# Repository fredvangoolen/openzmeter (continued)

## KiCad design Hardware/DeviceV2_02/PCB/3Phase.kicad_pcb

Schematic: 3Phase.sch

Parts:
BT1: JST 2mm-2P; JST_PH_B2B-PH-K_1x02_P2.00mm_Vertical
BZ1: QMB-09B-05; Buzzer_9x5.5RM4
C1, C2, C3, C4, C5, C6, C7, C10, C13, C14, C16, C17, C19, C20, C21, C22, C23, C24, C25, C26, C27, C28, C29, C30, C33, C34, C35, C36, C37: 100nF 25v; R_0603_1608Metric
C8, C9: 4.7uF 450v (10x12mm); CP_Radial_D10.0mm_P5.00mm
C11: 4.7uF 25v; C_0805_2012Metric
C12: 47uF 35v; CP_Radial_D5.0mm_P2.50mm
C15, C18, C31, C32: 100uF 16v; CP_Radial_D5.0mm_P2.50mm
D1, D3: ES1J; D_SMA
D2: BZT52C15S; D_SOD-323
D4, D5, D6: 1N4007G; D_SMA
D8: SS14; D_SMA
D9, D10, D12: 3mm bicolor LED; LED_D3.0mm
D11: 3mm blue LED; LED_D3.0mm
D13, D14: 1N5819WS; D_SOD-323
J1, J2, J3, J4: 95001-6P6C; KF2EDGR_2.54x4
J5: 2.54x3 pin header; PinHeader_1x03_P2.54mm_Vertical
J6: JST 2mm-2P; JST_PH_B2B-PH-K_1x02_P2.00mm_Vertical
JP1: 2.54x3 pin header; PinHeader_1x03_P2.54mm_Vertical
L1: 470uH 350mA; L_Axial_L12.0mm_D5.0mm_P5.08mm_Vertical_Fastron_MISC
L2: 1mH 300mA; CD75_7.8x7.0
L3: 10uH; CD43_4.5x4.0
L4: 2.2uH; CD32_3.5x3.0
P1: 3.81x4 terminal block; PhoenixContact_MC_1,5_4-G-3.81_1x04_P3.81mm_Horizontal
P2: 2 x 2.54x2 pin header; NanoPI Air
Q1: AP2301; SOT-23
Q2, Q3: 2N7002; SOT-23
R1, R2, R6, R9, R11, R13, R19, R20: 1k02; R_0603_1608Metric
R3, R7, R8, R14, R62, R63, R64: 100h; R_0603_1608Metric
R4, R5, R10, R12, R15, R16, R17, R22: 1k69; R_0603_1608Metric
R18, R21, R24, R25, R26, R27, R28, R29, R30: 200k; R_1206_3216Metric
R23, R35, R39, R40, R51, R52: 4k7; R_0603_1608Metric
R31, R32, R34: 2.2k; R_0603_1608Metric
R33: 36k5; R_0603_1608Metric
R36, R41, R42, R45, R46, R47, R48, R49, R57, R65, R66: 270k; R_0603_1608Metric
R37, R44, R56: 100k; R_0603_1608Metric
R38: 39h; R_0603_1608Metric
R43, R53, R54, R58: 1k43; R_0603_1608Metric
R50: 51k; R_0603_1608Metric
R55: 220h; R_0603_1608Metric
RV1: 05D391K; RV_Disc_D7mm_W3.4mm_P5mm
SW2: SW_Push; SW_Tactile_SKHH_Angled
TH1: NTC 10D5; RV_Disc_D7mm_W3.4mm_P5mm
U1, U3, U11: MCP6004; SOIC-14_3.9x8.7mm_P1.27mm
U2, U4, U5: ME6216A33M3G; SOT-23
U6: VIPER22ADIP-E; DIP-8_W7.62mm
U7: FP6715; TSOT-23-6
U8: SRV05-4; SOT-23-6
U9: 74HC4066; TSSOP-14_4.4x5mm_P0.65mm
U10: SY8201ABC; TSOT-23-6
U12: TP4054ST25P; SOT-23-5
U13: STM32F042; LQFP-32_7x7mm_Pitch0.8mm

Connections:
20v: C12.1, C17.1, D3.2 (A), L2.2, R40.1, U10.4 (EN), U10.5 (IN)
+1V65: C27.1, C33.1, C34.1, R5.2, R16.2, R17.2, R22.2, R31.2, R32.2, R34.2, R41.1, R42.1, R45.2, R46.2, R47.2, R48.2, R65.1, R66.1, U11.13 (-), U11.14, U13.7 (PA1)
+3.3VA: C1.1, C22.1, C32.1, R51.2, U2.2 (VO), U13.5 (VDDA)
+3V3: C23.1, C24.1, C31.1, R35.2, SW2.1, U4.2 (VO), U8.5, U13.1 (VDD), U13.17 (VDDIO2)
+5V: BZ1.1 (-), C14.1, C15.1, C25.2, C26.2, C30.2, C35.1, D13.2 (A), J6.1, JP1.3, P2.Vcc, R49.2, U1.4 (V+), U3.4 (V+), U5.3 (VI), U7.5 (OUT), U9.14 (V+), U11.4 (V+)
BAT_ADC: C37.1, R56.1, R57.1, U13.15 (ADC9)
CHRG: U12.1 (~CHRG), U13.18 (PA8)
GAIN_SW: U9.5 (ON), U9.6 (ON), U9.12 (ON), U9.13 (ON), U13.3 (PF1)
GND: BT1.2 (-), C1.2, C2.2, C3.2, C4.2, C6.2, C7.2, C8.2, C9.2, C12.2, C13.2, C14.2, C15.2, C16.2, C17.2, C18.2, C19.2, C20.2, C21.2, C22.2, C23.2, C24.2, C25.1, C26.1, C27.2, C28.1, C29.2, C30.1, C31.2, C32.2, C33.2, C34.2, C35.2, C36.2, C37.2, D1.2 (A), D11.1 (K), J1.1, J2.1, J3.1, J4.1, J5.3, P1.4, P2.GND, Q2.2 (S), Q3.2 (S), R23.2, R33.1, R37.1, R40.2, R44.1, R50.2, R52.2, R57.2, RV1.1, U1.11 (V-), U2.1 (GND), U3.11 (V-), U4.1 (GND), U5.1 (GND), U7.2 (GND), U8.2, U9.7 (V-), U10.2 (GND), U11.11 (V-), U12.2 (GND), U13.16 (GND), U13.32 (GND)
IN_L1: D6.2 (A), P1.3, R24.2
IN_L2: D5.2 (A), P1.2, R18.2
IN_L3: D4.2 (A), P1.1, R21.2
L1I_ADC: C6.1, R8.1, U8.1, U13.11 (ADC5)
L1V_ADC: C19.1, R62.1, U13.8 (ADC2)
L2I_ADC: C4.1, R3.1, U8.3, U13.12 (ADC6)
L2V_ADC: C20.1, R63.1, U13.9 (ADC3)
L3I_ADC: C2.1, R7.2, U8.6, U13.13 (ADC7)
L3V_ADC: C21.1, R64.1, U13.10 (ADC4)
NI_ADC: C7.1, R14.1, U8.4, U13.14 (ADC8)
unnamed: BT1.1 (+), Q1.3 (D), R56.2, U12.3 (OUT)
unnamed: BZ1.2 (+), Q2.3 (D)
unnamed: C5.1, L4.1, U10.6 (LX)
unnamed: C5.2, U10.1 (BST)
unnamed: C8.1, L1.1, RV1.2, TH1.1
unnamed: C9.1, L1.2, U6.5 (D1), U6.6 (D2), U6.7 (D3), U6.8 (D4)
unnamed: C10.1, D2.2 (A), U6.3 (FB)
unnamed: C10.2, C11.2, D1.1 (K), L2.1, U6.1 (S1), U6.2 (S2)
unnamed: C11.1, D2.1 (K), D3.1 (K), U6.4 (VDD)
unnamed: C16.1, R51.1, R52.1, U11.12 (+)
unnamed: C28.2, R39.2, U13.6 (WKUP1)
unnamed: C29.1, D13.1 (K), D14.1 (K), U2.3 (VI), U4.3 (VI)
unnamed: C36.1, JP1.1, U5.2 (VO)
unnamed: D4.1 (K), D5.1 (K), D6.1 (K), TH1.2
unnamed: D9.1 (A1), U13.28 (PB5)
unnamed: D10.1 (A1), U13.27 (PB4)
unnamed: D9.2 (K), D10.2 (K), D12.2 (K), R38.2
unnamed: D11.2 (A), R55.2
unnamed: D12.1 (A1), U13.25 (PA15)
unnamed: J1.2, R65.2, U1.5 (+)
unnamed: J1.3, R66.2, U1.10 (+)
unnamed: J1.4, J2.4, J3.4, J4.4, JP1.2
unnamed: J2.2, R42.2, U1.3 (+)
unnamed: J2.3, R41.2, U1.12 (+)
unnamed: J3.2, R45.1, U3.5 (+)
unnamed: J3.3, R46.1, U3.10 (+)
unnamed: J4.2, R47.1, U3.3 (+)
unnamed: J4.3, R48.1, U3.12 (+)
unnamed: J5.1, U13.24 (SWDCK)
unnamed: J5.2, U13.23 (SWDIO)
unnamed: J6.2, Q3.3 (D)
unnamed: L3.2, U7.1 (LX)
unnamed: P2.DM, U13.21 (USB-)
unnamed: P2.DP, U13.22 (USB+)
unnamed: Q2.1 (G), U13.26 (PB3)
unnamed: Q3.1 (G), R44.2, U13.31 (PB8/BOOT0)
unnamed: R1.1, R2.1, U1.8
unnamed: R1.2, R4.2, U1.6 (-), U9.8
unnamed: R2.2, R5.1, R43.2, U1.9 (-)
unnamed: R4.1, R8.2, U1.7
unnamed: R6.1, R9.1, U1.14
unnamed: R10.1, R13.2, U3.6 (-), U9.2
unnamed: R7.1, R10.2, U3.7
unnamed: R11.1, R13.1, U3.8
unnamed: R11.2, R17.1, R54.2, U3.9 (-)
unnamed: R3.2, R12.1, U1.1
unnamed: R9.2, R12.2, U1.2 (-), U9.10
unnamed: R14.2, R15.1, U3.1
unnamed: R15.2, R20.2, U3.2 (-), U9.4
unnamed: R6.2, R16.1, R53.2, U1.13 (-)
unnamed: R18.1, R27.2
unnamed: R19.1, R20.1, U3.14
unnamed: R19.2, R22.1, R58.2, U3.13 (-)
unnamed: R21.1, R28.2
unnamed: R23.1, U12.5 (PROG)
unnamed: R24.1, R25.1
unnamed: R25.2, R29.2
unnamed: R26.1, R34.1, U11.10 (+)
unnamed: R26.2, R28.1
unnamed: R27.1, R30.2
unnamed: R29.1, R31.1, U11.3 (+)
unnamed: R30.1, R32.1, U11.5 (+)
unnamed: R35.1, U13.4 (~RST)
unnamed: R38.1, U13.20 (PA10)
unnamed: R39.1, SW2.2
unnamed: R43.1, U9.9
unnamed: R49.1, R50.1, U7.3 (FB)
unnamed: R53.1, U9.11
unnamed: R54.1, U9.1
unnamed: R55.1, U13.19 (PA9)
unnamed: R58.1, U9.3
unnamed: R62.2, U11.1, U11.2 (-)
unnamed: R63.2, U11.6 (-), U11.7
unnamed: R64.2, U11.8, U11.9 (-)
POWER: C13.1, D8.1 (K), D14.2 (A), L3.1, Q1.2 (S), U7.6 (VIN)
POWER_EN: R37.2, U7.4 (EN), U13.29 (PB6)

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
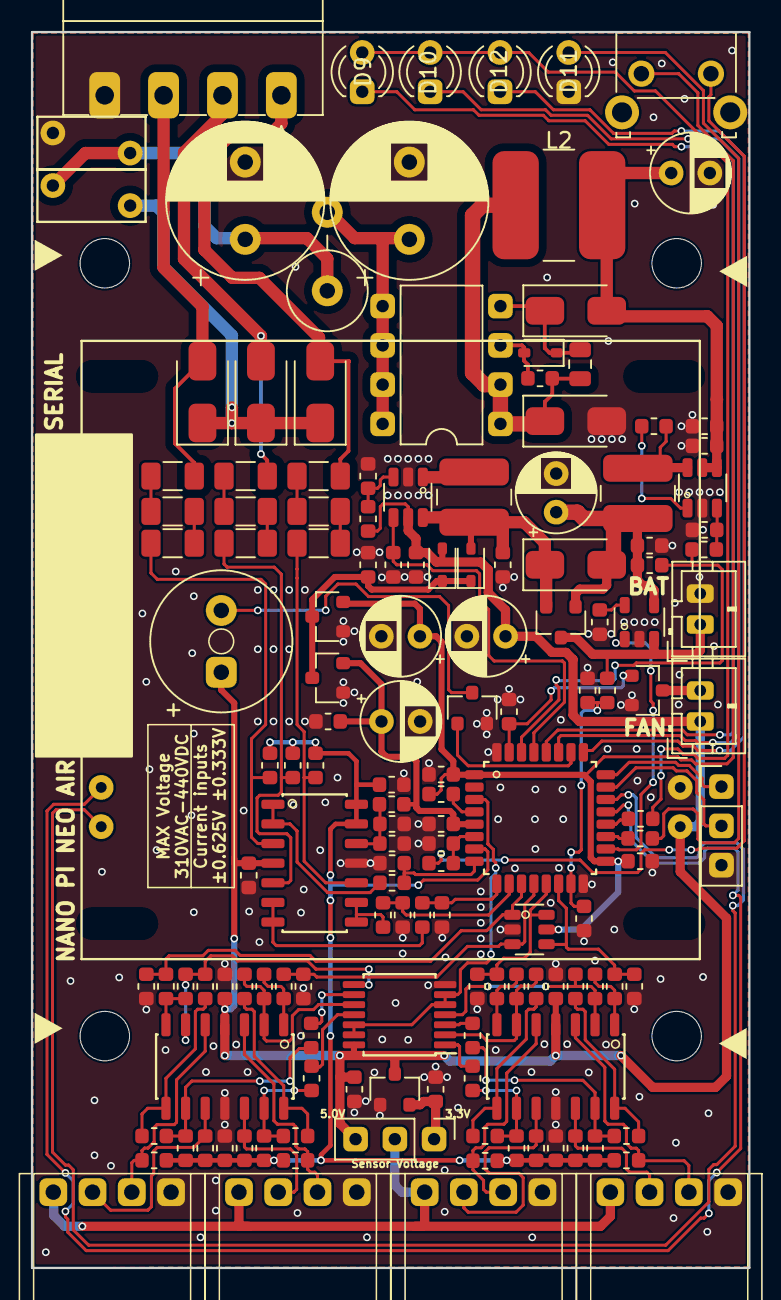
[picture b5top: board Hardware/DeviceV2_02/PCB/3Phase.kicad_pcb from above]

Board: 2 copper layers, 46.4 x 80.0 mm, 152 parts (0 on the bottom side), 98 nets.

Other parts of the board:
R59: 150k; R_0603_1608Metric
‣: MountingHole_3.2mm_M3
‣#2, ‣#3, ‣#4: MountingHole_3.2mm_M3

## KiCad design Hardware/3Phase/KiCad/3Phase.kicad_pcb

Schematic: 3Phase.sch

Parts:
BT1: Battery_Cell; JST_PH_B2B-PH-K_1x02_P2.00mm_Vertical
BZ1: Buzzer; Buzzer_12x9.5RM7.6
C1, C2, C4, C6, C7, C13, C14, C19, C20, C21, C22, C23, C25, C26, C27, C28, C29: 100nF; C_0603_1608Metric
C3, C17: 100nF 50v; C_0603_1608Metric
C5, C16, C24: C_Small; C_0603_1608Metric
C8, C9: 3.3uF 450v; CP_Radial_D10.0mm_P5.00mm
C10: 47nF 50v; C_0603_1608Metric
C11: 2.2uF 25v; C_0805_2012Metric
C12: 47uF 25v; CP_Radial_D5.0mm_P2.50mm
C15: 100uF 10v; CP_Radial_D4.0mm_P2.00mm
C18: 100uF 16v; CP_Radial_D5.0mm_P2.50mm
D1: ES1J; D_SMA
D2: BZT52C15S; D_SOD-323
D3: SF18; D_SMA
D4, D5, D6: 1N4007; D_SMA
D7: 1N4148; D_SOD-323
D8: SS14; D_SMA
D9, D10, D12: 3mm bicolor LED; LED_D3.0mm
D11: 3mm blue LED; LED_D3.0mm
D13, D14: 1N5819WS; D_SOD-323
J1, J2, J3, J4: 95001-6P6C; RJ11_4P4C
J5: Conn_01x03; PinHeader_1x03_P2.54mm_Vertical
L1: 470uH 350mA; L_Axial_L12.0mm_D5.0mm_P5.08mm_Vertical_Fastron_MISC
L2: 1mH 300mA; L_Radial_D10.5mm_P5.00mm_Abacron_AISR-01
L3: 10uH; CD43_4.5x4.0
L4: 2.2uH; CD32_3.5x3.0
L5: 10uH; L_0603_1608Metric
P1: CONN_01X04; PhoenixContact_MC_1,5_4-G-3.81_1x04_P3.81mm_Horizontal
P2: NanoPI AIR; NanoPI Air
Q1: Si2301DS; SOT-23
Q2: 2N7002; SOT-23
R1, R9, R33: 33k; R_0603_1608Metric
R2, R4, R5, R6, R11, R12, R16, R17, R23, R35, R39, R51, R52: 10k; R_0603_1608Metric
R3, R7, R8, R14, R62, R63, R64: 100h; R_0603_1608Metric
R10, R15, R19, R22: 10K; R_0603_1608Metric
R13, R20: 33K; R_0603_1608Metric
R18, R21, R24, R25, R26, R27, R28, R29, R30: 200k; R_1206_3216Metric
R31, R32, R34: 2.2k; R_0603_1608Metric
R36: 240k; R_0603_1608Metric
R37, R43, R44, R56: 100k; R_0603_1608Metric
R38: 180h; R_0603_1608Metric
R41, R42, R45, R46, R47, R48, R65, R66: 1M; R_0603_1608Metric
R49: 300k; R_0603_1608Metric
R50: 56k; R_0603_1608Metric
R55: 39h; R_0603_1608Metric
R57: 270k; R_0603_1608Metric
R58, R59, R60, R61: 1k5; R_0603_1608Metric
RV1: 07D431K; RV_Disc_D7mm_W3.6mm_P5mm
SW1: SW_Push; SW_SPST_FSMSM
SW2: SW_Push; SW_Tactile_SKHH_Angled
TH1: NTC 10D5; RV_Disc_D7mm_W3.6mm_P5mm
U1, U11: MCP6004; SOIC-14_3.9x8.7mm_P1.27mm
U2: 4066; SOIC-14_3.9x8.7mm_P1.27mm
U3: MCP6004; SOIC-14_3.9x8.7mm_Pitch1.27mm
U4: XC6206; SOT-23
U6: VIPer22; DIP-8_W7.62mm
U7: PS7516; TSOT-23-6
U10: SY8113; TSOT-23-6
U12: LTC4054; SOT-23-5
U13: STM32F042; LQFP-32_7x7mm_Pitch0.8mm

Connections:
15v: C12.1, C17.1, D3.2, L2.2, U10.4, U10.5
+1V65: R5.2, R16.2, R17.2, R22.2, R31.2, R32.2, R34.2, R41.1, R42.1, R45.2, R46.2, R47.2, R48.2, R65.1, R66.1, U11.1, U11.2 (-)
+3.3VA: C1.1, C22.1, C25.2, C26.2, C27.1, L5.2, R51.2, U1.4 (V+), U2.14 (V+), U3.4 (V+), U11.4 (V+), U13.5 (VDDA)
+3V3: C23.1, C24.1, L5.1, R35.2, R43.1, U4.2, U13.1 (VDD), U13.17 (VDDIO2)
+5V: BZ1.1, C14.1, C15.1, D13.2, J1.4, J2.4, J3.4, J4.4, P2.Vcc, R49.2, U7.5
BAT_ADC: R56.1, R57.1, U13.15 (ADC9)
CHRG: U12.1, U13.18 (PA8)
EXT: R33.2, R36.2, U10.3, U13.30 (PB7)
GND: BT1.2, C1.2, C2.2, C3.2, C4.2, C6.2, C7.2, C8.2, C9.2, C12.2, C13.2, C14.2, C15.2, C16.2, C17.2, C18.2, C19.2, C20.2, C21.2, C22.2, C23.2, C24.2, C25.1, C26.1, C27.2, C28.1, C29.2, D1.2, D11.1, J1.1, J2.1, J3.1, J4.1, J5.3, P1.1, P2.GND, Q2.2 (S), R23.2, R33.1, R37.1, R44.1, R50.2, R52.2, R57.2, RV1.1, SW1.1, SW2.1, U1.11 (V-), U2.7 (V-), U3.11 (V-), U4.1, U7.2, U10.2, U11.11 (V-), U12.2, U13.16 (GND), U13.32 (GND)
IN_L1: D6.2, P1.2, R24.2
IN_L2: D5.2, P1.3, R18.2
IN_L3: D4.2, P1.4, R21.2
L1I_ADC: C6.1, R8.1, U13.11 (ADC5)
L1V_ADC: C19.1, R62.1, U13.8 (ADC2)
L1_GAIN: U2.13 (ON), U13.7 (PA1)
L2I_ADC: C4.1, R3.1, U13.12 (ADC6)
L2V_ADC: C20.1, R63.1, U13.9 (ADC3)
L2_GAIN: R44.2, U2.5 (ON), U13.31 (PB8/BOOT0)
L3I_ADC: C2.1, R7.2, U13.14 (ADC8)
L3V_ADC: C21.1, R64.1, U13.10 (ADC4)
L3_GAIN: U2.6 (ON), U13.2 (PF0)
NI_ADC: C7.1, R14.1, U13.13 (ADC7)
N_GAIN: U2.12 (ON), U13.3 (PF1)
unnamed: BT1.1, Q1.3, R56.2, U12.3
unnamed: BZ1.2, Q2.3 (D)
unnamed: C5.1, L4.1, U10.6
unnamed: C5.2, U10.1
unnamed: C8.1, L1.1, RV1.2, TH1.1
unnamed: C9.1, L1.2, U6.5, U6.6, U6.7, U6.8
unnamed: C10.1, D2.2, U6.3
unnamed: C10.2, C11.2, D1.1, L2.1, U6.1, U6.2
unnamed: C11.1, D7.1, U6.4
unnamed: C16.1, R51.1, R52.1, U11.3 (+)
unnamed: C3.1, C18.1, D8.2, L4.2, Q1.1, R36.1, U12.4
unnamed: C28.2, R39.2, R43.2, U13.6 (WKUP1)
unnamed: C29.1, D13.1, D14.1, U4.3
unnamed: D2.1, D3.1, D7.2
unnamed: D4.1, D5.1, D6.1, TH1.2
unnamed: D9.1 (A1), U13.28 (PB5)
unnamed: D10.1 (A1), U13.27 (PB4)
unnamed: D9.2 (K), D10.2 (K), D12.2 (K), R38.2
unnamed: D11.2, R55.2
unnamed: D12.1 (A1), U13.26 (PB3)
unnamed: J1.2, R66.2, U1.3 (+)
unnamed: J1.3, R65.2, U1.12 (+)
unnamed: J2.2, R41.2, U1.5 (+)
unnamed: J2.3, R42.2, U1.10 (+)
unnamed: J3.2, R45.1, U3.3 (+)
unnamed: J3.3, R46.1, U3.12 (+)
unnamed: J4.2, R48.1, U3.5 (+)
unnamed: J4.3, R47.1, U3.10 (+)
unnamed: J5.1, U13.23 (SWDIO)
unnamed: J5.2, U13.24 (SWDCK)
unnamed: L3.2, U7.1
unnamed: P2.DM, U13.21 (USB-)
unnamed: P2.DP, U13.22 (USB+)
unnamed: Q2.1 (G), U13.25 (PA15)
unnamed: R1.1, R4.1, U1.13 (-), U2.1
unnamed: R1.2, R2.1, R58.2, U1.1
unnamed: R2.2, R5.1, U1.2 (-)
unnamed: R4.2, R8.2, U1.14
unnamed: R6.1, R9.2, U1.7, U2.3
unnamed: R7.1, R10.1, U3.14
unnamed: R10.2, R13.1, U2.8, U3.13 (-)
unnamed: R11.1, R13.2, R60.2, U3.1
unnamed: R11.2, R17.1, U3.2 (-)
unnamed: R9.1, R12.1, R59.1, U1.9 (-)
unnamed: R3.2, R12.2, U1.8
unnamed: R14.2, R15.2, U3.8
unnamed: R15.1, R20.1, R61.1, U3.9 (-)
unnamed: R6.2, R16.1, U1.6 (-)
unnamed: R18.1, R27.2
unnamed: R19.1, R20.2, U2.10, U3.7
unnamed: R19.2, R22.1, U3.6 (-)
unnamed: R21.1, R28.2
unnamed: R23.1, U12.5
unnamed: R24.1, R25.1
unnamed: R25.2, R29.2
unnamed: R26.1, R34.1, U11.10 (+)
unnamed: R26.2, R28.1
unnamed: R27.1, R30.2
unnamed: R29.1, R31.1, U11.12 (+)
unnamed: R30.1, R32.1, U11.5 (+)
unnamed: R35.1, SW1.2, U13.4 (~RST)
unnamed: R38.1, U13.20 (PA10)
unnamed: R39.1, SW2.2
unnamed: R49.1, R50.1, U7.3
unnamed: R55.1, U13.19 (PA9)
unnamed: R58.1, U2.2
unnamed: R59.2, U2.4
unnamed: R60.1, U2.9
unnamed: R61.2, U2.11
unnamed: R62.2, U11.13 (-), U11.14
unnamed: R63.2, U11.6 (-), U11.7
unnamed: R64.2, U11.8, U11.9 (-)
POWER: C13.1, D8.1, D14.2, L3.1, Q1.2, U7.6
POWER_EN: R37.2, U7.4, U13.29 (PB6)

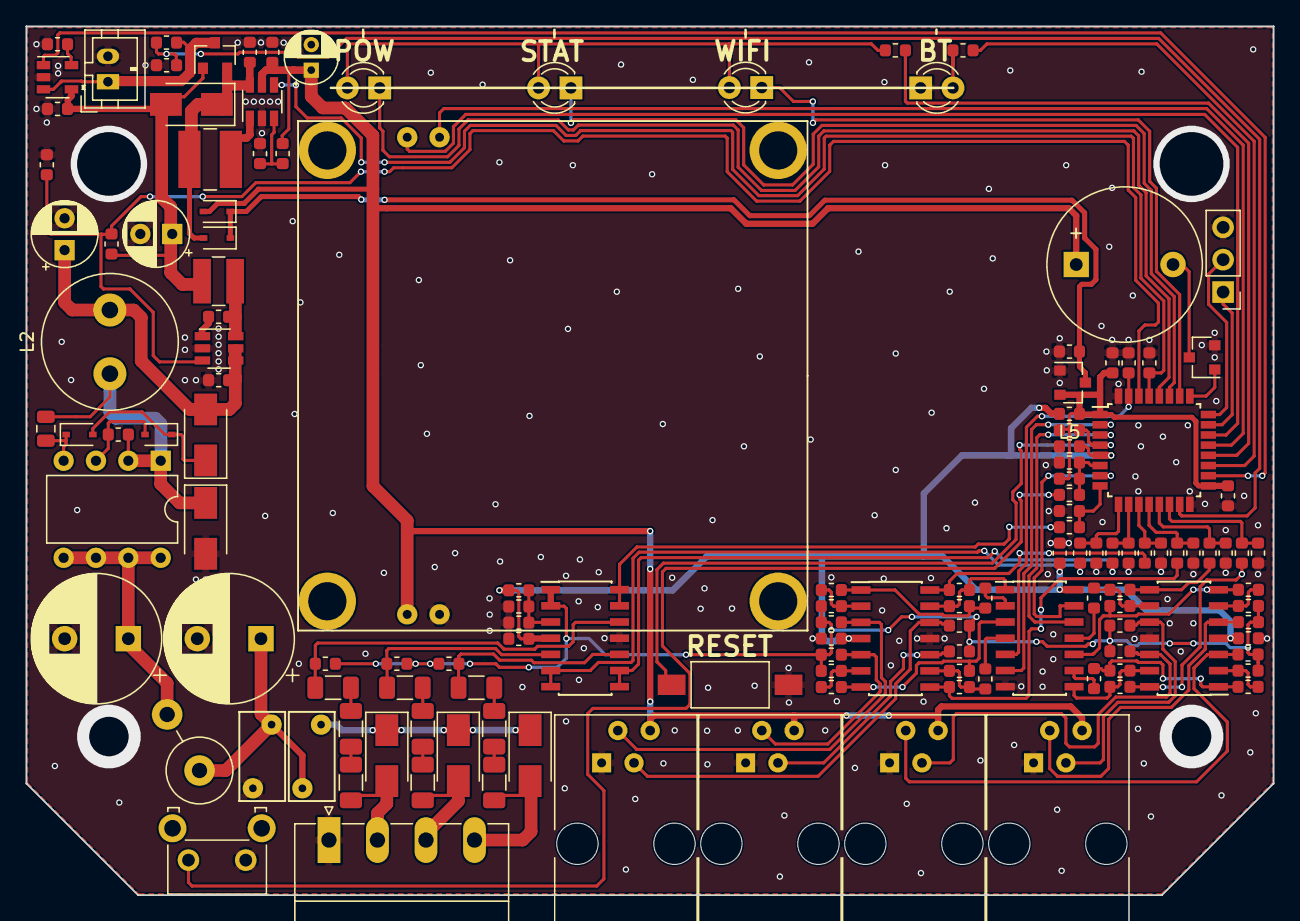
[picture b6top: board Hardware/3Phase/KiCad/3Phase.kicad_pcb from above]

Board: 2 copper layers, 97.9 x 68.2 mm, 136 parts (0 on the bottom side), 97 nets.

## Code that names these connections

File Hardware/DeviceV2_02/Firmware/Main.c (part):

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#define RECV_EP                         0x02
// Types definition ----------------------------------------------------------------------------------------------------
typedef struct {
  uint16_t Power_Color:2;     //Power LED (PB5) Red when off but plugged, off if off and not plugged, green if running and yellow if booting or shuttingdown
  uint16_t Status_Color:2;    //Status LED (PB4) Green if service running, yellow on events (cleared by software), red on service lost communication or errors.
  uint16_t Wifi_Color:2;      //Wifi LED (PB3) Green if connected to internet, yellow if connected to network, red if no connection
  uint16_t Bluetooth_Color:1; //Bluetooth LED (PA9) On when bluetooth enabled
  uint16_t Buzzer:9;          //Buzzer beeps
} SignalsStatus_t;
enum LED_Color {OFF = 0, RED = 1, GREEN = 2, YELLOW = 3 };
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    }
  }
  if(Samples_Buffer.Counter == 0) {
    GPIOA->BSRR = GPIO_BSRR_BS_10 | GPIO_BSRR_BS_15;    //A mode (PA10=1)
    GPIOB->BSRR = GPIO_BSRR_BS_5 | GPIO_BSRR_BS_4;
    GPIOA->BSRR = (SignalsStatus.Bluetooth_Color) ? GPIO_BSRR_BS_9 : GPIO_BSRR_BR_9;
    if(SignalsStatus.Power_Color & RED) GPIOB->BSRR |= GPIO_BSRR_BR_5;
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    }
    Samples_Buffer.Counter++;
  } else if(Samples_Buffer.Counter == 12) {
    GPIOA->BSRR = GPIO_BSRR_BR_10 | GPIO_BSRR_BR_15 | GPIO_BSRR_BR_9;    //A mode (PA10=0)
    GPIOB->BSRR = GPIO_BSRR_BR_5 | GPIO_BSRR_BR_4;
    if(SignalsStatus.Power_Color & GREEN) GPIOB->BSRR |= GPIO_BSRR_BS_5;
    if(SignalsStatus.Status_Color & GREEN) GPIOB->BSRR |= GPIO_BSRR_BS_4;
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  RCC->APB1ENR |= RCC_APB1ENR_USBEN | RCC_APB1ENR_CRSEN | RCC_APB1ENR_PWREN | RCC_APB1ENR_TIM2EN | RCC_APB1ENR_TIM3EN;
  RCC->APB2ENR |= RCC_APB2ENR_SYSCFGCOMPEN | RCC_APB2ENR_ADC1EN;
  CRS->CR |= CRS_CR_AUTOTRIMEN | CRS_CR_CEN;
  //Configure port F (PF1 -> Digital outputs)
  GPIOF->MODER   |= GPIO_MODER_MODER1_0;
  GPIOF->OSPEEDR |= GPIO_OSPEEDER_OSPEEDR0 | GPIO_OSPEEDER_OSPEEDR1;
  //Configure Port A (PA0, PA8 -> Digital inputs, PA9, PA10, PA15 -> Digital outputs, PA1, PA2, PA3, PA4, PA5, PA6, PA7 -> Analog input, PA11, PA12 -> Alternate function, PA13, PA14 -> SWD)
  GPIOA->MODER |= GPIO_MODER_MODER1 | GPIO_MODER_MODER2 | GPIO_MODER_MODER3 | GPIO_MODER_MODER4 | GPIO_MODER_MODER5 | GPIO_MODER_MODER6 | GPIO_MODER_MODER7 | GPIO_MODER_MODER9_0 |
                  GPIO_MODER_MODER10_0 | GPIO_MODER_MODER11_1 | GPIO_MODER_MODER12_1 | GPIO_MODER_MODER15_0;
  GPIOA->PUPDR |= GPIO_PUPDR_PUPDR8_0 | GPIO_PUPDR_PUPDR0_1;
  //Configure Port B (PB7 -> Digital input, PB0, PB1 -> Analog inputs, PB4, PB5, PB6 -> Digital output, PB3, PB8 -> Alternate function)
  GPIOB->MODER |= GPIO_MODER_MODER0 | GPIO_MODER_MODER1 | GPIO_MODER_MODER3_1 | GPIO_MODER_MODER8_1 | GPIO_MODER_MODER4_0 | GPIO_MODER_MODER5_0 | GPIO_MODER_MODER6_0;
  GPIOB->AFR[0] |= 0x00002000; //PB3 -> TIM2_CH2
  //Enable DMA controller
  DMA1_Channel1->CPAR = (uint32_t)&ADC1->DR;
  DMA1_Channel1->CMAR = (uint32_t)ADC_Read;
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
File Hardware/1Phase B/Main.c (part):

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  while(MS_Ticks < End);
}
// Hardware init =======================================================================================================
//LEDs(PA8 PA9 PA10 PF6 PF7 PA15 PB3 PB4 PB5 PB6 PB7 PB8 PB9 - Rows PC13 PC14) Buzzer(PA0) NonoPI(PA2) ExtPower(PB2) BatCharge(PA3) BatLevel(PA1) Buttons(PD8 PC15)
void Interface_Config() {
  RCC_AHBPeriphClockCmd(RCC_AHBPeriph_GPIOA | RCC_AHBPeriph_GPIOB | RCC_AHBPeriph_GPIOC | RCC_AHBPeriph_GPIOD | RCC_AHBPeriph_GPIOF, ENABLE);
  GPIO_InitTypeDef GPIO_InitStructure;
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
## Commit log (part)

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2020-08-26 Bluetooth related API added to swagger docs
2020-08-26 NTP related API added to swagger docs
2020-09-01 Added missing files in previous commit
2020-09-01 Added new ticker for energy bars graph, now hour(Quarter) format is used, bars are aligned from hour start to end. Legend adjusted to center of bar. Time line also improved to show on hours boundary,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
2020-09-03 Power/energy graphs can now mix points with 15m and 1h granularity in single graph to show hourly energy and period names for example. Export tested and fixed in all analysis views
2020-09-05 Added ESIOS API docs
2020-09-05 Added WIFI API docs
2020-09-08 Changes in "Cost" view. Some fixs in labels, units and minor bugs in web. Database manager changed to retry connections (if postgre do not shutdown correctly it take some time to start on next reboot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
2020-09-09 Some changes in DeviceV2_02 driver allow to increase buffer size 230%. This reduce lost sample chance a lot.
2020-09-13 Device battery level added to web page
2020-09-16 Missing char in "Reactive_Energy" fix Omega2 build enviroment ready and tested Fix in bluetooth interface name fix Dashboard do not load on 3PHASE+N mode fix
2020-09-16 Missing files
2020-09-16 HTTPLib updated. Bugs in events retrieval solved. Bugs in vis-timeline solved. Some others bugs in js packages solved.
2020-09-23 Modbus repaired. Working again in remote access.
2020-10-01 Add Cyclic Histogram/Jolt frontend
2020-10-02 CH: Don't record phase 0, location 0 (due to interpolation always putting this point at y=0)
2020-10-08 'Remote access' do not work as desired using http as transport. I will try to use a raw socket to bidirectional json message communication.
2020-10-14 After some time without push...
    Remote function improved, it now support last streaming functions.
    Lots of small bugs, typos and minor changes.
    Working in series name in API, to make request and reply consistent.
    Added some series to API getSeries and getSeriesNow to retrieve harmonics in real/complex in 1m and 200ms.
    MQTT stream harmonics too.
    MODBus now works but need some changes to access to remote devices.
2020-10-15 Analyzers Tags format corrected
2020-10-15 Edit/delete events bugs solved
2020-10-15 Events now displayed
2020-10-20 Changes in httplib waiting PR to be merged Remote should work.
2020-10-26 CH: Fix type error
2020-10-27 Remove unneeded param
2020-10-27 some changes to compile on omega2, however it have no power to run analyzers. Lots of routers use MIPS arch and they can run ozm as "Remote" server for internal ozms in net. Working in "physical" sol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
2020-10-27 Missing file in previous commit
2020-10-27 Missing char
2020-10-28 getAlarmsDef modified getAlarmDef removed addAlarmDef and setAlarmDef documentation added to swagger
2020-11-09 Updating http lib
2020-11-09 yhirose lib fails again with last merge, this workaround make it works temporally
2020-11-17 Added R59 to DeviceV2_02 BOM (Close #128) Added API call evalRates to support for external calculation of rates (Close #127) Telegram config now work (Close #124)
2020-11-20 Fixs in evalRates
2020-11-20 Taxs typo corrected in some places.
2020-12-10 New hardware added 'DeviceV2_03', compatible with V2_02 but with new power supply design, added RTC and ethernet port.
2020-12-30 Some bugs in rate editor fixed. Progress bar added to stats views. This views download entire year and load may take some seconds. Some changes in WRLocks to fix deadlocks. Progress in DeviceV2_03.
2021-01-07 Working in #56, all data can be exported as json. Some bug related with chunks loading solved. Minor changes in API
2021-01-14 webpack changed to allow relative path
2021-01-15 EN50160 view repaired
2021-01-18 Analyzers database intertions enqueued instead insert then in database directly, this reduce block analysis time and reduce the chance of lost samples.
2021-01-20 Working in #104, almost done.
2021-01-20 Missing files added
2021-01-28 Rates finally moved from database to analyzer config. Rates pre parsed on configure to improve later calls. Some checkings added and previous known bugs fixed.
2021-01-29 Do not save logo in config file if equal to default one
2021-01-31 Most log messages revised, lot more added. Database can read columns by index inproving up a bit speed in rate calculations
2021-02-08 Lot of bugs and small improvements (#133) Add suport for deletion of samples or entire event Add frontent buttons to delete alarms Add compression for maintenance dialog Bugs in maintenance dialog so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
2021-02-15 Some changes in permissions model integration. Some bugs fixed in WEB. libfft statically linked in executable to reduce footprint. Installation image ready (uboot+squashfs in 16M), in future it can b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
2021-02-22 Changes to system status view. Some corrections
2021-03-02 SetSeries API added, this allow restore backups from WEB and remote sync funcions. Lots of refactor in analyzer class to reuse existing code of AnalyzerSoft in AnalyzerRemote and other future analyze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
2021-03-04 Remote sync almost ready... all functions works, testing all page sections and fixing issues.
2021-03-07 Some fix, working in API docs.
2021-03-08 DeviceV2 Leds works. Some fixs in power view.
2021-03-08 Working in API docs
2021-03-09 Working in detailed API descriptions.
2021-03-15 More API functions documentation added. Other bugs fixed. Alarms and events retrieve by last change added to backend (front pendding)
2021-03-15 Added missing file and removed unused dependency
2021-03-18 Wifi dialog fixed and improved to show connection messages. VPN dialog improved to show connection messages. Syslog showed in Help/System view WifiManager, NTPManager and VPNManager changed to use uc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
2021-03-19 Some bugs in remote solved
2021-03-19 API docs directory missing.
2021-03-23 Working in CBOR API communication. All works as expected, transfer size reduce to about half the size in reation to JSON. HTTPRequest class added to make programming easy. All transfer/parsing/checki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
2021-03-29 CBOR integration. All API call accept JSON/CBOR as input and output. WEB page use CBOR by default, sync/remote functions use CBOR too. Some API than previously send only 200 status and no content now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
2021-04-04 Save events and alarms in remote sync is working. Added toast messages to web. Bugs in rates calc solved. Some more checkings added to remote sync blocks. Some issues in CBOR communication solved.
2021-04-07 WifiManager changed. Only interface name required.
2021-04-09 Common error handler added to all Post in WEB. No internet dialog works again
2021-04-09 Some dependencies removed (as data is downloaded as cbor, no need to compress it in maintenance view) Maintenance progress shown in toast.
2021-04-12 GetSeriesNow API added Some API docs updates TaskPool class added to manage all task in the project, this replace old model where all threads are created and sleep until a work unit arrive. Working i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
2021-04-17 GetSeriesNow and GetStatus calls wait few seconds if no avaliable data cached in remote analyzer.
2021-04-19 Unused folder removed
2021-04-22 Added some logs messages to find device reconfigure lock Added DC blocking filter to DeviceV2 (Not fully testes, no config option added yet)
2021-04-26 Close #56, in maintenance data can be exported as json or CBOR
2021-04-26 200MS added to export
2021-05-05 Wavestream function works again (only in local analyzers)
2021-05-05 Some more debug messages
2021-05-07 changes in Analyzer to reduce blocking time. some minor fix in page and other class working in DeviceV2_03 hardware
2021-05-17 Añadido el firmware del solar al repo Algunos cambios en el driver del V2 para reducir un pocoel uso de CPU Añadido driver del V3
2021-05-17 Added missing files
2021-05-18 El solar lee!, ya esta listo el firmware, el driver de captura, todo el tema de enrutado de canales, el analyzer adaptado... solo queda la calibracion generica.
2021-05-23 Changes in makefile to use branch name in build.
    Added downsampling in Waveform stream to allow streaming in low speed links (allowed ratios are samplefreq/1, 2, 3...
    Some functions changed to allow const to be used.
    ConsumerQueue sinchronization problems solved, both consumer functions merged into one.
    Some unused code removed and some error checking added.
2021-06-03 Filter is used and should be used in many places of code, a new and improved classes are added. DCFilter class work correctly, Bandpass is still WIP, it need some math work to compute muti stage filt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
2021-06-04 A bug in Tariff editor fixed, adding ESP_2.0TD_2021
2021-06-04 More changes in service, 2phase and 2phase+n is ready... now working in front end to make all graph works again
2021-06-05 API docs updated to add 2PHASE and 2PHASE+N
    Frontend updates to handle 2PHASE and 2PHASE+N
    Some changes to handle different phase counts more easily
2021-06-06 Lot of dead code removed in frontend
    All views changed to support new 2phase modes
    AnalyzerV2 dialog and backend need some more changes to allow 2phase mode selection
2021-06-07 Some bugs in V2 configurator
2021-06-21 Bugs in WEB solved New filter class corrections. Low pass added as option to DeviceV2 config Some dead code removed
2021-06-22 Libhttp updated
2021-06-22 Added ESP_2.0TD (Maximeter) tariff template (under testing)
2021-06-22 Bugs in Cost view solved
2021-06-23 Changes to ESP_2.0TD (Maximeter) tariff Bugs in cost view(Power)
2021-07-06 Some bugs in service solved Working in DeviceV2_03 PCB
2021-07-09 Add Cyclic Histogram and Jolt algorithm backend and frontend
2021-07-13 Some changes in WIFI settings dialog, now bluetooth connection stay open while saving settings. Dome changes to Conectivity tab in settings. Autoupdate finished. Now openZmeter downloads new versions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
2021-07-14 Change in Gitlab CI
2021-07-14 Improv-wifi is initialy designed for esphome/esp32, trying to make it works under linux/bluez stack Currently only unordered source code is copied
2021-07-25 GATT configurator is really really hard to implement in bluez. It may work in future. However a HTML wizard is added to easily configure ozm throw bluetooth. Now no login is required and user see thi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
    Some other code clean in WEB, and some work in deviceV2_03 firmware.
2021-07-28 (WIP) Begin adding Ideal waveform filtering
2021-08-04 CH: Add Initial config options
2021-08-04 CH: reduce network bandwidth for histogram requests
2021-08-04 Config updates
2021-08-09 Working in deviceV2_03 firmware
2021-08-12 WIP: Begin adding support for current CH, restructure array for JSON get request
2021-08-18 Deleted unused/deprecated/testing hardware devices. Keep only active ones.
2021-08-22 Makefile changes to force correct date/time version tagging on building
2021-09-15 Testing
2021-09-15 Remove testing
2021-09-15 Revert "Testing"
    This reverts commit 6827c1de26d1fbee1c45f0c868d4883336b03873.
2021-09-17 First attemp to replace bootstrap/jquery/vuetable2 and all controls with quasar. Its works pretty well and look beutifull but take me lot of time, i will work on this from time to time. Currently onl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
2021-09-20 Changes in interface
2021-09-22 Converted login form to quasar
2021-09-27 Debugging CH
2021-09-27 More debugging
2021-10-09 Working in Quasar
2021-10-09 More changes
2021-10-09 getDevices API changes
2021-10-27 Most API tools in JS done, adding some more functions Working in UI Added D3.js to allow more advanced and fast graphs
2021-11-08 Heatmap works ok
2021-11-12 Save to change to other branch
2021-12-26 Basic structure of views ported to quasar.
    Selector for Year ported.
    Selector for Aggregs ported.
2022-01-03 Working in views components and some structure changes
2022-01-18 Working in SVG cubism like component, almost done. Changing components to use quasar
2022-01-25 Lo ultimo que tengo de Quasar
2022-01-31 Changes to use Solar device
2022-02-14 Working
2022-03-08 Replaced some components and fixed expands buttons in bash
